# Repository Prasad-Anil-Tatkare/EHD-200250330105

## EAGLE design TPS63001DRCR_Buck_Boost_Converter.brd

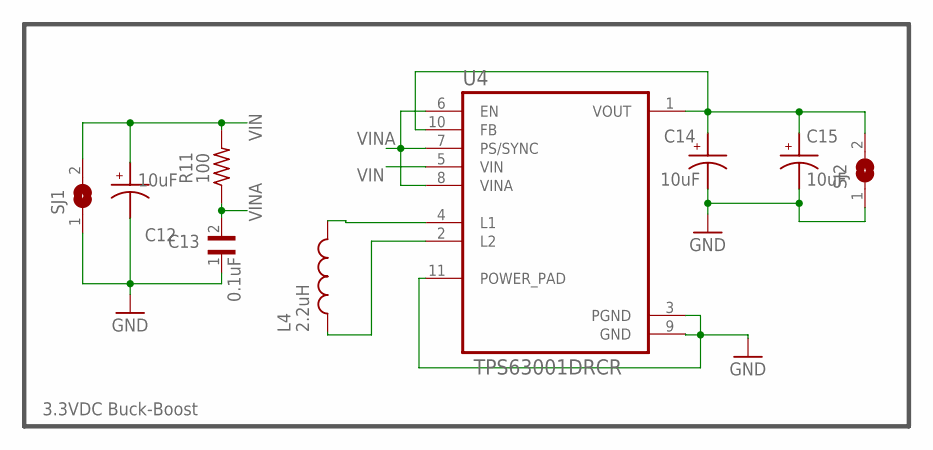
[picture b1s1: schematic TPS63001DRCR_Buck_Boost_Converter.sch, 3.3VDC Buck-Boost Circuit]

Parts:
C12, C14, C15: 10uF; CAPAE430X550N
C13: 0.1uF; CAPC1608X100N
L4: 2.2uH; INDC1608X95N
R11: 100; RESC2012X65N
SJ1, SJ2: SJW
U4: TPS63001DRCR; VREG_V62/16624-01YE

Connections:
3.3VDC: C14.1, C15.1, SJ2.2, U4.1 (VOUT), U4.10 (FB)
GND: C12.2, C13.1, C14.2, C15.2, SJ1.1, SJ2.1, U4.3 (PGND), U4.9 (GND), U4.11 (POWER_PAD)
unnamed: L4.2, U4.4 (L1)
unnamed: L4.1, U4.2 (L2)
VIN: C12.1, R11.2, SJ1.2, U4.5 (VIN)
VINA: C13.2, R11.1, U4.6 (EN), U4.7 (PS/SYNC), U4.8 (VINA)

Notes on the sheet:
3.3VDC Buck-Boost

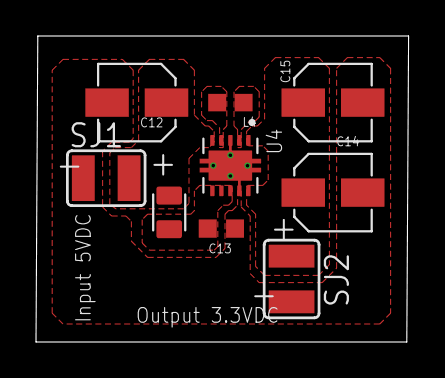
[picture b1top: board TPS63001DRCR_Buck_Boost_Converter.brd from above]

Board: 2 copper layers, 20.7 x 17.0 mm, 9 parts (0 on the bottom side), 6 nets.

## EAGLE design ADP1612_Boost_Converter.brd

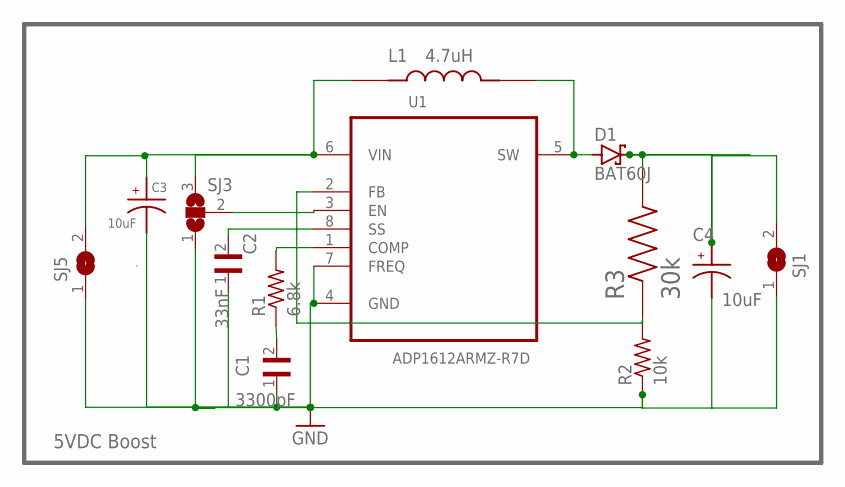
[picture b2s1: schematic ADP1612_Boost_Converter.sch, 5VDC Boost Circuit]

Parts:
C1: 3300pF; CAPC0603X33N
C2: 33nF; CAPC2012X95N
C3, C4: 10uF; CAPAE430X550N
D1: BAT60J; SOD323_ST
L1: 4.7uH; IND_LQH43NZ4R7M03L
R1: 6.8k; RESC2012X65N
R2: 10k; RESC2012X65N
R3: 30k; RESC6332X65N
SJ1, SJ5: SJW
SJ3: SJ2WW; SJ_2W
U1: ADP1612ARMZ-R7D; SOIC-08

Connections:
5VDC: C4.1, D1.C, R3.2, SJ1.2
GND: C1.1, C2.1, C3.2, C4.2, R2.1, SJ1.1, SJ3.1, SJ5.1, U1.4 (GND), U1.7 (FREQ)
unnamed: C3.1, L1.1, SJ3.3, SJ5.2, U1.6 (VIN)
unnamed: C1.2, R1.1
unnamed: R1.2, U1.1 (COMP)
unnamed: C2.2, U1.8 (SS)
unnamed: D1.A, L1.2, U1.5 (SW)
unnamed: R2.2, R3.1, U1.2 (FB)
unnamed: SJ3.2, U1.3 (EN)

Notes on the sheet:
5VDC Boost

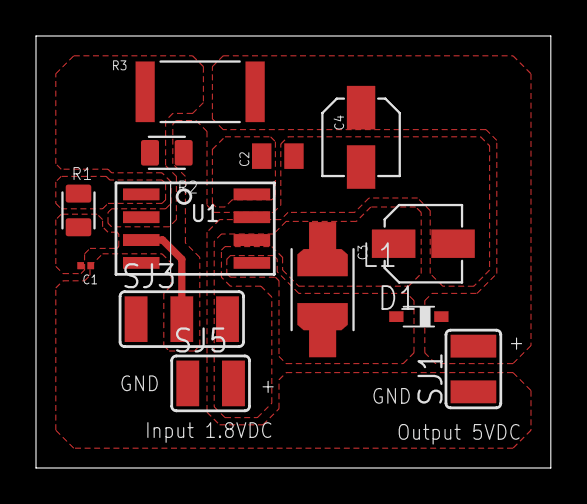
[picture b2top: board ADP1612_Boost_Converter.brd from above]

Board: 2 copper layers, 28.6 x 24.0 mm, 13 parts (0 on the bottom side), 9 nets.

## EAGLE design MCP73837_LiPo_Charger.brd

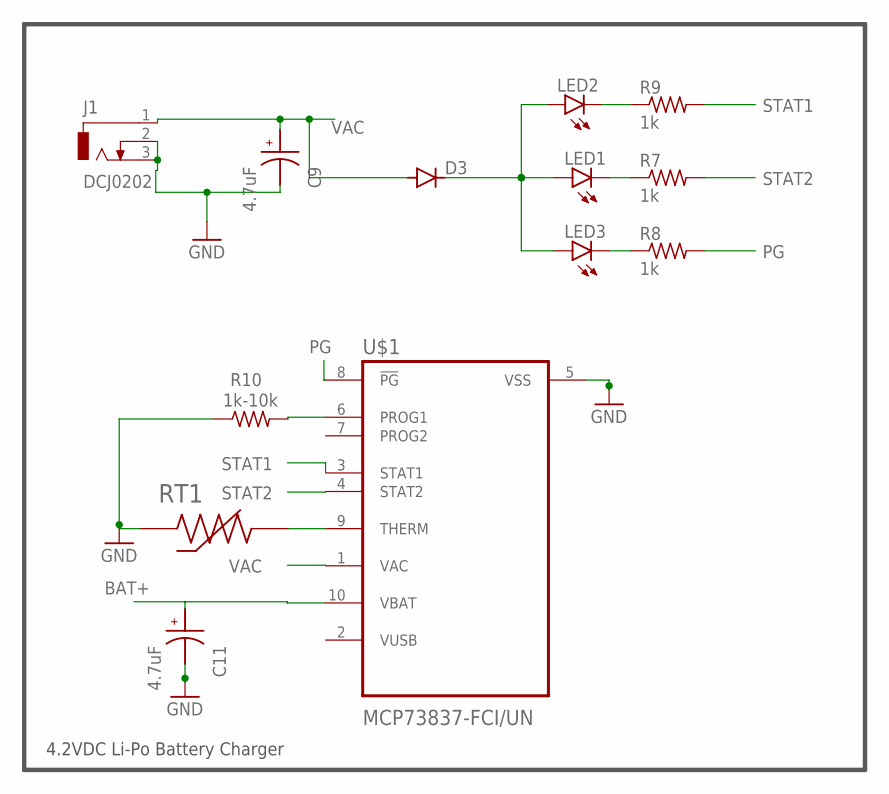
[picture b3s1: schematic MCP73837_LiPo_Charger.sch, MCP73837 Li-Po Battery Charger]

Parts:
C9, C11: 4.7uF; CAPAE430X550N
D3: DIODE-DO214BA; DO214BA
J1: DCJ0202
LED1, LED2, LED3: LEDCHIP-LED0805; CHIP-LED0805
R7, R8, R9: 1k; RESC2012X65N
R10: 1k-10k; RESC2012X65N
RT1: NCP18XW223E03RB; THRMC1608X95N
U$1: MCP73837-FCI/UN; SOP50P490X110-10N

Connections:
BAT+: C11.1, U$1.10 (VBAT)
GND: C9.2, C11.2, J1.2, J1.3, R10.1, RT1.1, U$1.5 (VSS)
unnamed: D3.C, LED1.A, LED2.A, LED3.A
unnamed: LED2.C, R9.1
unnamed: LED1.C, R7.1
unnamed: LED3.C, R8.1
unnamed: R10.2, U$1.6 (PROG1)
unnamed: RT1.2, U$1.9 (THERM)
PG: R8.2, U$1.8 (!PG)
STAT1: R9.2, U$1.3 (STAT1)
STAT2: R7.2, U$1.4 (STAT2)
VAC: C9.1, D3.A, J1.1, U$1.1 (VAC)

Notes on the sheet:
4.2VDC Li-Po Battery Charger

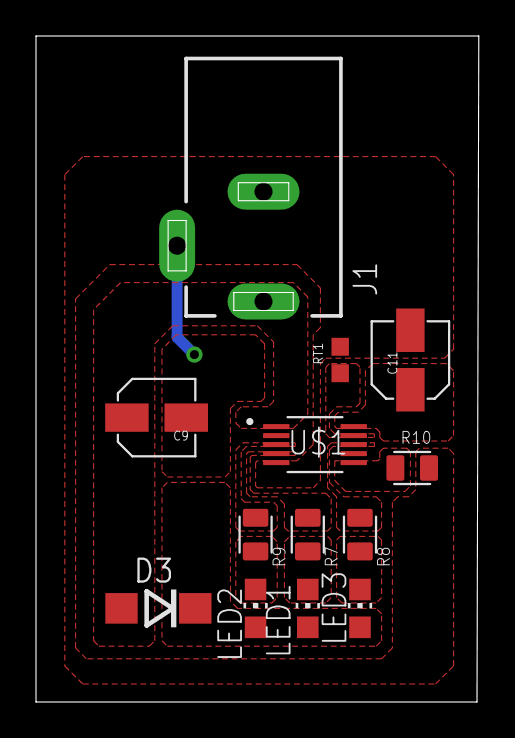
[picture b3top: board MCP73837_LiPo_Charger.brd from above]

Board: 2 copper layers, 24.6 x 37.0 mm, 13 parts (0 on the bottom side), 12 nets.

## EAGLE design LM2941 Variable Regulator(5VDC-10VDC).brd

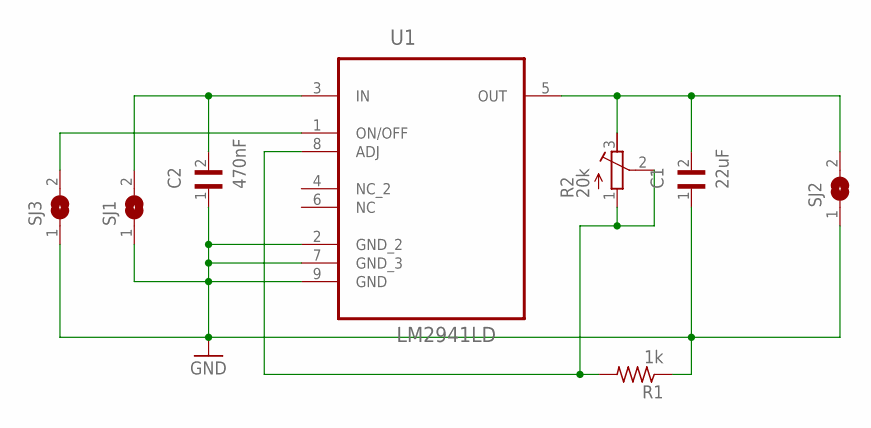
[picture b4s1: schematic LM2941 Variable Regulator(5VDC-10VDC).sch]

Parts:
C1: 22uF; CAPC6153X390N
C2: 470nF; CAPC1608X90N
R1: 1k; R0805
R2: 20k; RTRIM3214W
SJ1, SJ2, SJ3: SJW
U1: LM2941LD; DFN400X400X80-9N

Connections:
GND: C1.1, C2.1, R1.1, SJ1.1, SJ2.1, SJ3.1, U1.2 (GND_2), U1.7 (GND_3), U1.9 (GND)
unnamed: C2.2, SJ1.2, U1.3 (IN)
unnamed: R1.2, R2.1 (A), R2.2 (S), U1.8 (ADJ)
unnamed: C1.2, R2.3 (E), SJ2.2, U1.5 (OUT)
unnamed: SJ3.2, U1.1 (ON/OFF)

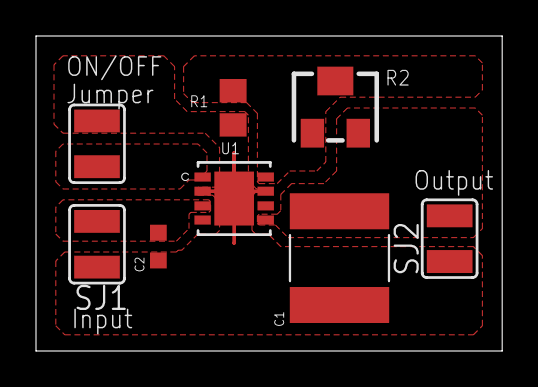
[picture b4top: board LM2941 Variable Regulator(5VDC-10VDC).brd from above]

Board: 2 copper layers, 25.9 x 17.5 mm, 8 parts (0 on the bottom side), 5 nets.

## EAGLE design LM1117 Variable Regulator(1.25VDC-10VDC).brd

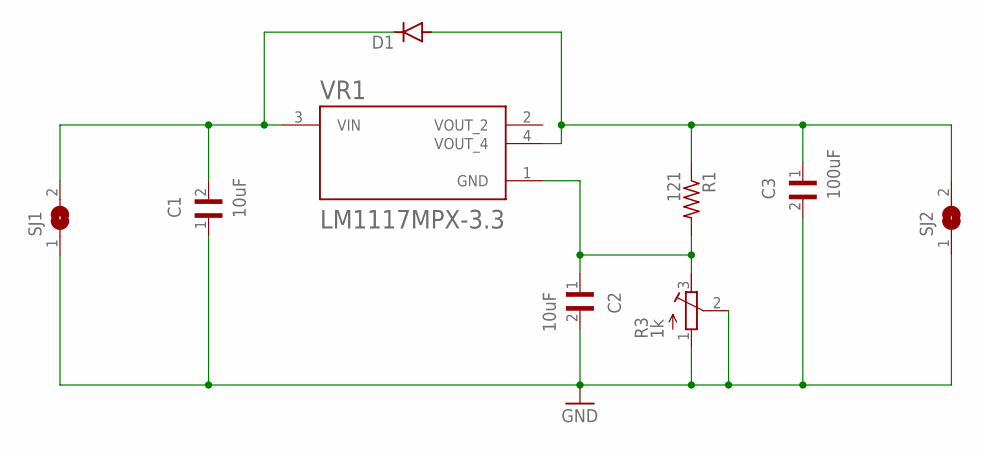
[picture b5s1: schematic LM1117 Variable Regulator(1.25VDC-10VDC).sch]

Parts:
C1, C2: 10uF; CAPC1608X100N
C3: 100uF; CAPPM7343X310N
D1: DIODE-DO-214AC; DO-214AC
R1: 121; R1206
R3: 1k; RTRIM3214W
SJ1, SJ2: SJW
VR1: LM1117MPX-3.3; VREG_LM1117MPX-3.3

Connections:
GND: C1.1, C2.2, C3.2, R3.1 (A), R3.2 (S), SJ1.1, SJ2.1
unnamed: C1.2, D1.C, SJ1.2, VR1.3 (VIN)
unnamed: C3.1, D1.A, R1.1, SJ2.2, VR1.4 (VOUT_4)
unnamed: C2.1, R1.2, R3.3 (E), VR1.1 (GND)

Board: 2 copper layers, 9 parts (0 on the bottom side), 4 nets, no tracks yet.

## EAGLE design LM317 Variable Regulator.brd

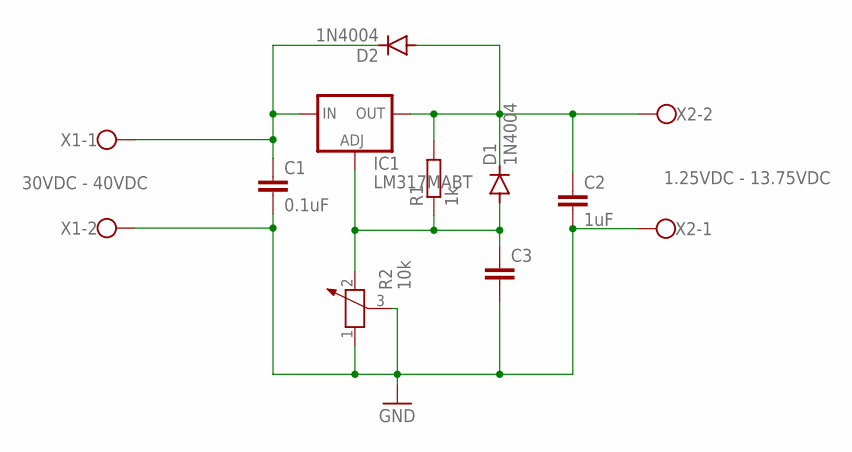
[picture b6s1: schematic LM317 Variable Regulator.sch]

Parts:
C1: 0.1uF; C025-024X044
C2: 1uF; C025-024X044
C3: C-EU025-024X044; C025-024X044
D1, D2: 1N4004; DO41-10
IC1: LM317MABT; TO220L1
R1: 1k; 0204/7
R2: 10k; PT-10
X1: 30VDC - 40VDC; W237-102
X2: 1.25VDC - 13.75VDC; W237-102

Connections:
GND: C1.2, C2.2, C3.2, R2.1, R2.3, X1.2, X2.1
unnamed: C1.1, D2.C, IC1.3 (IN), X1.1
unnamed: C2.1, D1.C, D2.A, IC1.2 (OUT), R1.2, X2.2
unnamed: C3.1, D1.A, IC1.1 (ADJ), R1.1, R2.2

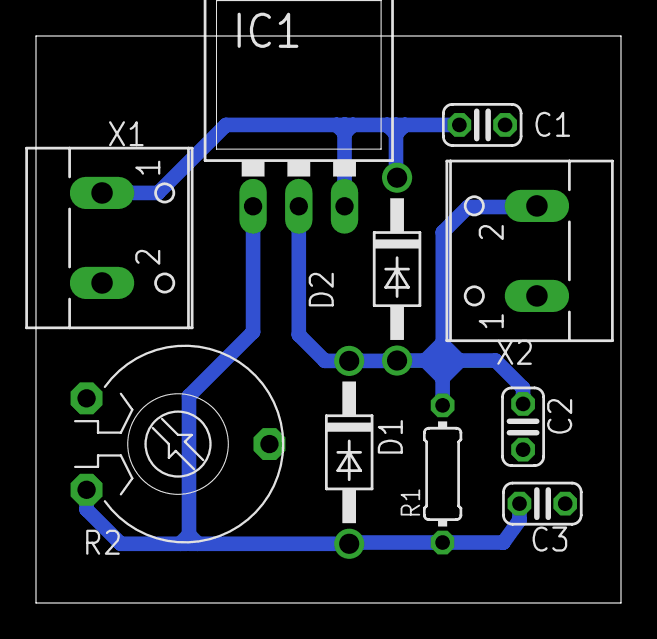
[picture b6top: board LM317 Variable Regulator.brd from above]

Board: 2 copper layers, 32.5 x 31.5 mm, 10 parts (0 on the bottom side), 4 nets.

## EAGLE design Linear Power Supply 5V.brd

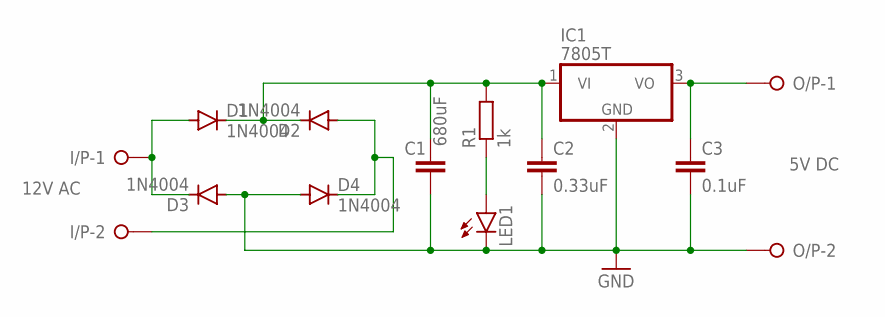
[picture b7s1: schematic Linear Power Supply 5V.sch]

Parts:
C1: 680uF; C025-060X050
C2: 0.33uF; C025-060X050
C3: 0.1uF; C025-060X050
D1, D2, D3, D4: 1N4004; DO41-10
I/P: 12V AC; W237-132
IC1: 7805T; TO220H
LED1: LED3MM
O/P: 5V DC; W237-132
R1: 1k; 0207/12

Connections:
GND: C1.2, C2.2, C3.2, D3.A, D4.A, IC1.2 (GND), LED1.K (C), O/P.2
unnamed: D1.A, D3.C, I/P.1
unnamed: C1.1, C2.1, D1.C, D2.C, IC1.1 (VI), R1.2
unnamed: LED1.A, R1.1
unnamed: C3.1, IC1.3 (VO), O/P.1
unnamed: D2.A, D4.C, I/P.2

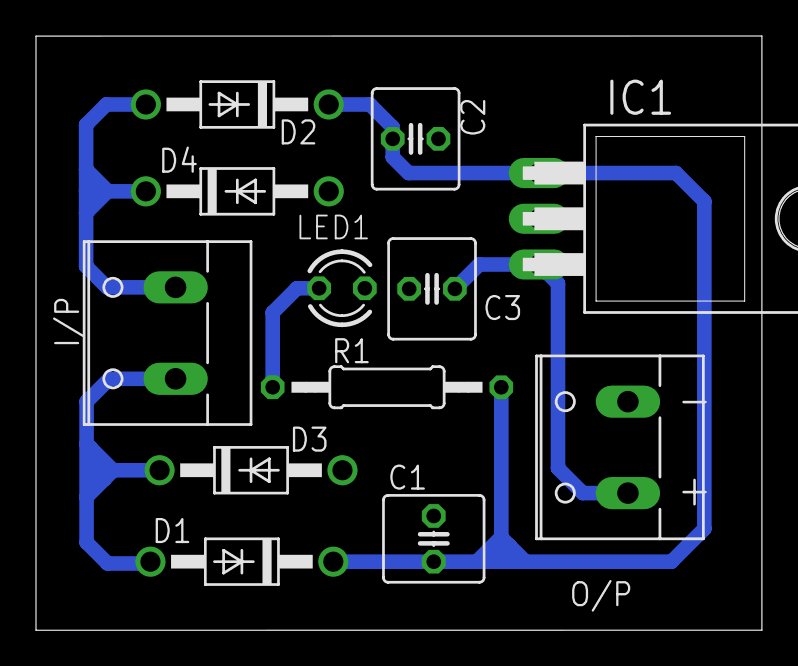
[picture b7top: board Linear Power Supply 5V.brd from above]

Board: 2 copper layers, 40.3 x 33.0 mm, 12 parts (0 on the bottom side), 6 nets.

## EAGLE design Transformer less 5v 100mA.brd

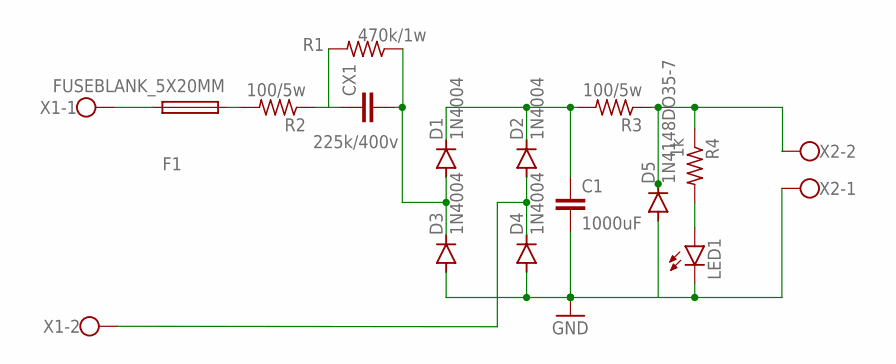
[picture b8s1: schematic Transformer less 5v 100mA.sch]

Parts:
C1: 1000uF; C025-060X050
CX1: 225k/400v; XC15B10
D1, D2, D3, D4: 1N4004; DO41-10
D5: 1N4148DO35-7; DO35-7
F1: FUSEBLANK_5X20MM; FUSE_HOLDER_5X20MM
LED1: LED5MM
R1: 470k/1w; 0414/15
R2, R3: 100/5w; 0617/22
R4: 1k; 0207/7
X1, X2: W237-102

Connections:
GND: C1.2, D3.A, D4.A, D5.A, LED1.K (C), X2.1
unnamed: F1.1, X1.1
unnamed: F1.2, R2.2
unnamed: CX1.1, R1.2, R2.1
unnamed: C1.1, D1.C, D2.C, R3.2
unnamed: D5.C, R3.1, R4.1, X2.2
unnamed: CX1.2, D1.A, D3.C, R1.1
unnamed: LED1.A, R4.2
unnamed: D2.A, D4.C, X1.2

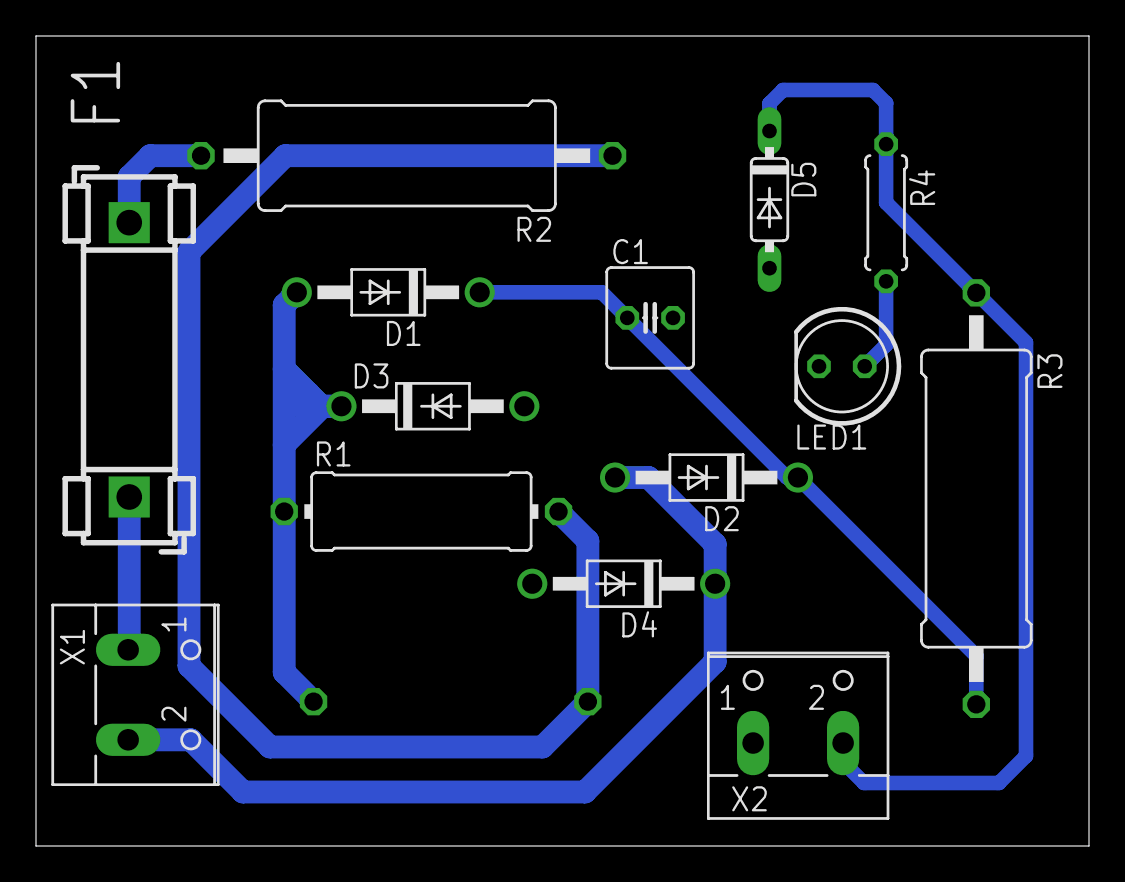
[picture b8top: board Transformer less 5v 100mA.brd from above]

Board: 2 copper layers, 58.5 x 45.0 mm, 15 parts (1 on the bottom side), 9 nets.
